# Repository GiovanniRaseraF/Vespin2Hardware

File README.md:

# Hardware
## Modulo LM2596S
### Autors
- Cristofoli Nicola : Schematics
- Rasera Giovanni : PCB layout

-

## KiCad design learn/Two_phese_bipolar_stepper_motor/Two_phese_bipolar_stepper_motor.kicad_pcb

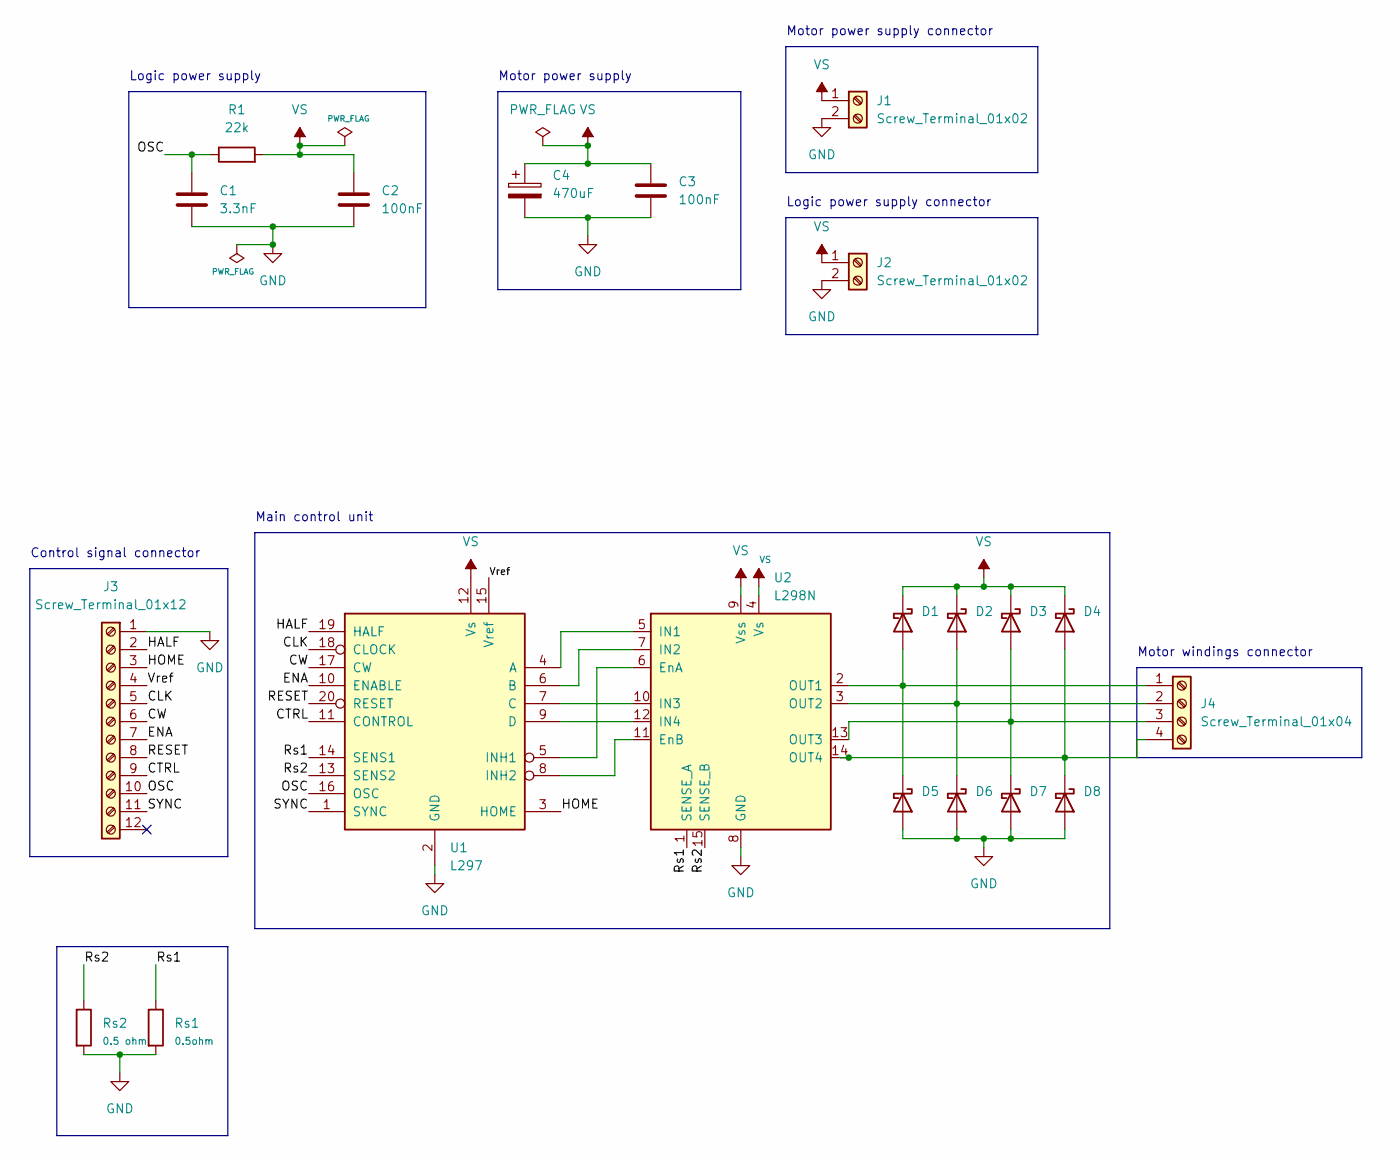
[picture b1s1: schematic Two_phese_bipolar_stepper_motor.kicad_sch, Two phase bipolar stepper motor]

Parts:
C1: 3.3nF; C_Rect_L10.0mm_W3.0mm_P7.50mm_FKS3_FKP3
C2, C3: 100nF; C_Rect_L7.5mm_W6.5mm_P5.00mm
C4: 470uF; CP_Radial_D13.0mm_P5.00mm
D1, D2, D3, D4, D5, D6, D7, D8: D_DO-27_P15.24mm_Horizontal
J1, J2: Screw_Terminal_01x02; TerminalBlock_Phoenix_MKDS-1,5-2-5.08_1x02_P5.08mm_Horizont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
J3: Screw_Terminal_01x12; TerminalBlock_Phoenix_MKDS-1,5-12_1x12_P5.00mm_Horizontal
J4: Screw_Terminal_01x04; TerminalBlock_Phoenix_MKDS-1,5-4_1x04_P5.00mm_Horizontal
R1: 22k; R_Axial_DIN0922_L20.0mm_D9.0mm_P25.40mm_Horizontal
Rs1: 0.5ohm; R_Axial_DIN0414_L11.9mm_D4.5mm_P15.24mm_Horizontal
Rs2: 0.5 ohm; R_Axial_DIN0414_L11.9mm_D4.5mm_P15.24mm_Horizontal
U1: L297; DIP-20_W7.62mm_LongPads
U2: L298N; TO-220-15_P2.54x2.54mm_StaggerOdd_Lead4.58mm_Vertical

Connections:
/CLK: J3.5, U1.18 (CLOCK)
/CTRL: J3.9, U1.11 (CONTROL)
/CW: J3.6, U1.17 (CW)
/ENA: J3.7, U1.10 (ENABLE)
/HALF: J3.2, U1.19 (HALF)
/HOME: J3.3, U1.3 (HOME)
/OSC: C1.1, J3.10, R1.1, U1.16 (OSC)
/RESET: J3.8, U1.20 (RESET)
/Rs1: Rs1.1, U1.14 (SENS1), U2.1 (SENSE_A)
/Rs2: Rs2.1, U1.13 (SENS2), U2.15 (SENSE_B)
/SYNC: J3.11, U1.1 (SYNC)
/Vref: J3.4, U1.15 (Vref)
GND: C1.2, C2.2, C3.2, C4.2, D5.2 (A), D6.2 (A), D7.2 (A), D8.2 (A), J1.2, J2.2, J3.1, Rs1.2, Rs2.2, U1.2 (GND), U2.8 (GND)
unnamed: D1.2 (A), D5.1 (K), J4.1, U2.2 (OUT1)
unnamed: D2.2 (A), D6.1 (K), J4.2, U2.3 (OUT2)
unnamed: D3.2 (A), D7.1 (K), J4.3, U2.13 (OUT3)
unnamed: D4.2 (A), D8.1 (K), J4.4, U2.14 (OUT4)
unnamed: U1.4 (A), U2.5 (IN1)
unnamed: U1.6 (B), U2.7 (IN2)
unnamed: U1.7 (C), U2.10 (IN3)
unnamed: U1.9 (D), U2.12 (IN4)
unnamed: U1.5 (INH1), U2.6 (EnA)
unnamed: U1.8 (INH2), U2.11 (EnB)
VS: C2.1, C3.1, C4.1, D1.1 (K), D2.1 (K), D3.1 (K), D4.1 (K), J1.1, J2.1, R1.2, U1.12 (Vs), U2.4 (Vs), U2.9 (Vss)

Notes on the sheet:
Logic power supply
Motor power supply connector
Main control unit
Motor power supply
Motor windings connector
Control signal connector
Logic power supply connector

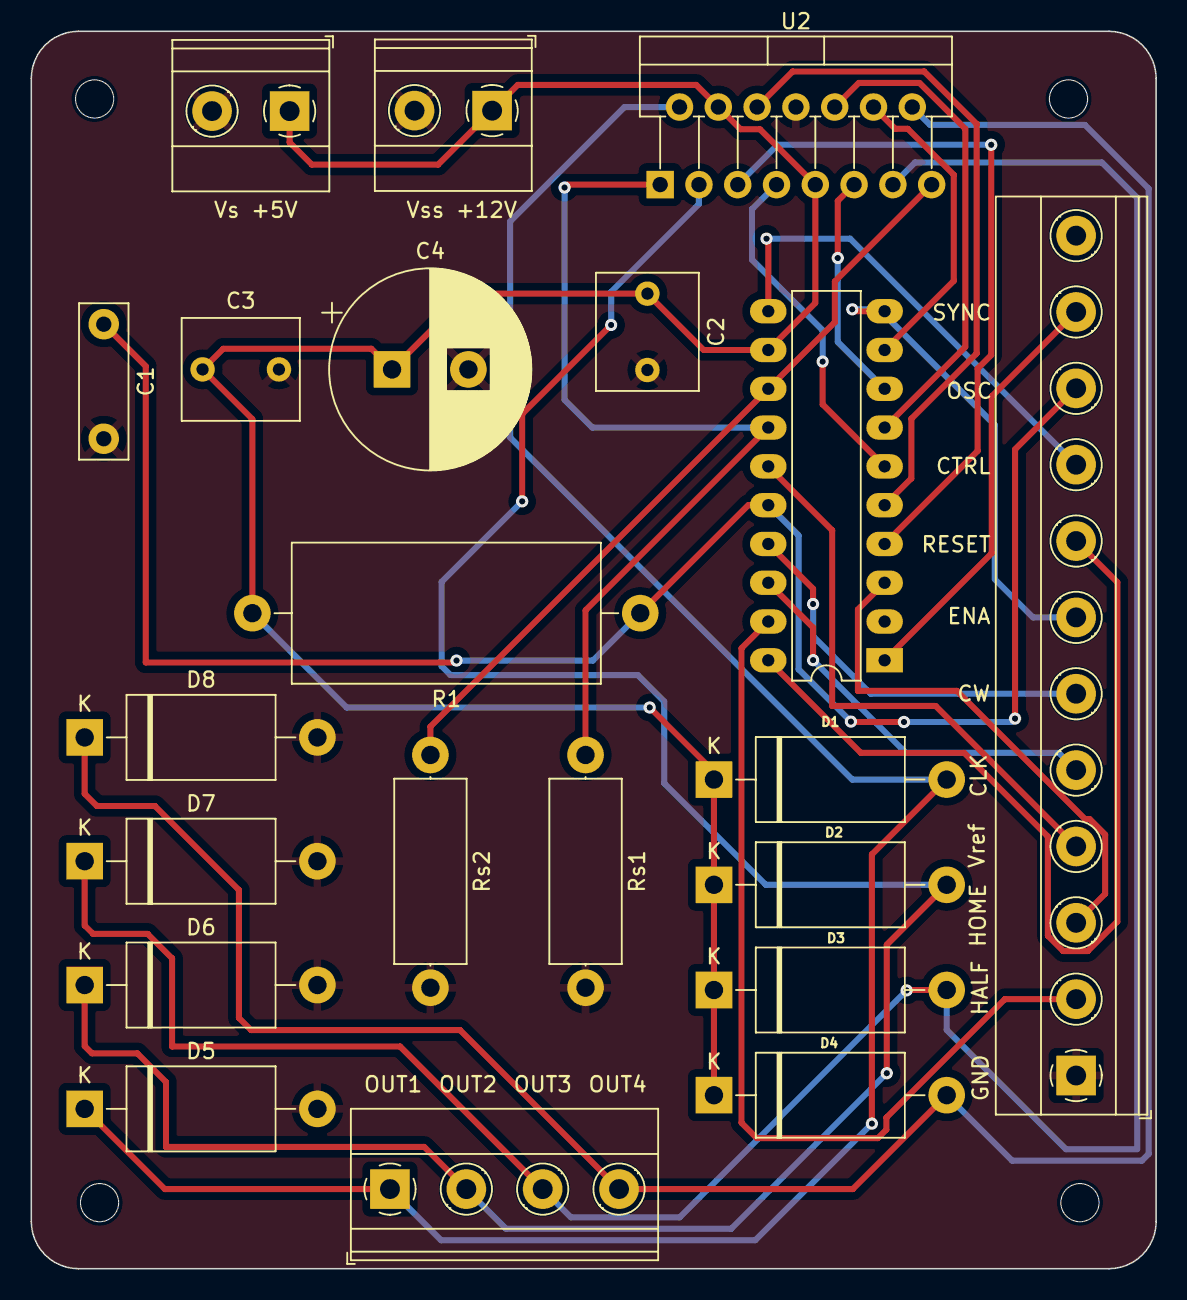
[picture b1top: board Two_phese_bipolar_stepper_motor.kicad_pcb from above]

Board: 2 copper layers, 73.7 x 81.0 mm, 21 parts (0 on the bottom side), 24 nets.

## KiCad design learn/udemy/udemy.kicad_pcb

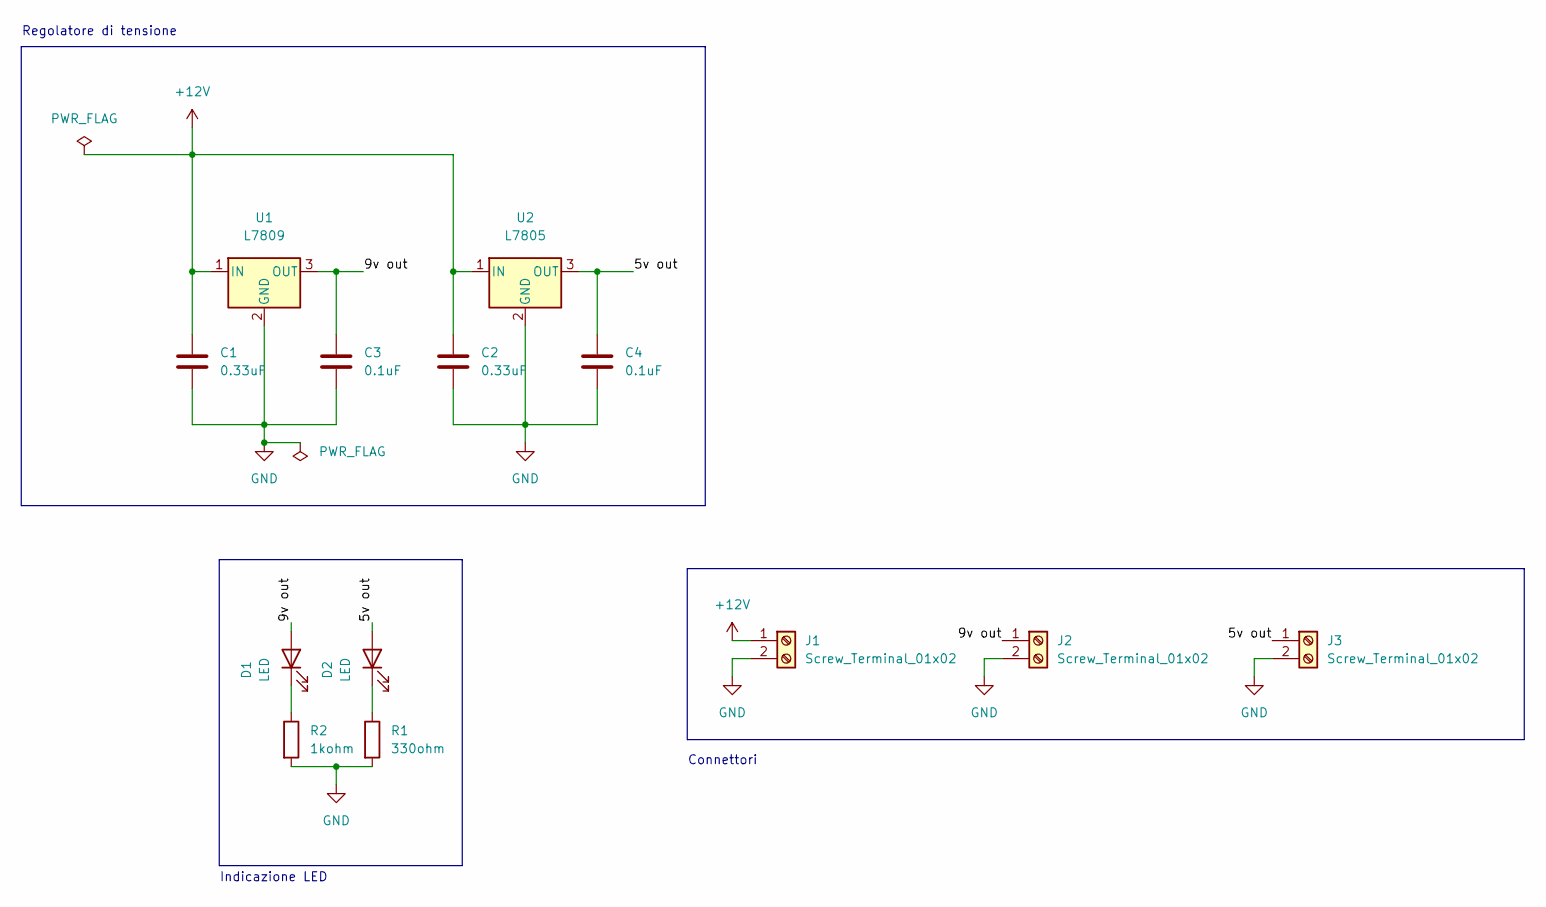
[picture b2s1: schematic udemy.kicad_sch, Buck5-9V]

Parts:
C1, C2: 0.33uF; C_Disc_D4.7mm_W2.5mm_P5.00mm
C3, C4: 0.1uF; C_Disc_D3.0mm_W2.0mm_P2.50mm
D1, D2: LED; LED_D4.0mm
J1, J2, J3: Screw_Terminal_01x02; TerminalBlock_Phoenix_MKDS-1,5-2-5.08_1x02_P5.08mm_Horizont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
R1: 330ohm; R_Axial_DIN0204_L3.6mm_D1.6mm_P5.08mm_Horizontal
R2: 1kohm; R_Axial_DIN0207_L6.3mm_D2.5mm_P7.62mm_Horizontal
U1: L7809; TO-220-3_Vertical
U2: L7805; TO-220-3_Vertical

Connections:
+12V: C1.1, C2.1, J1.1, U1.1 (IN), U2.1 (IN)
/5v out: C4.1, D2.2 (A), J3.1, U2.3 (OUT)
/9v out: C3.1, D1.2 (A), J2.1, U1.3 (OUT)
GND: C1.2, C2.2, C3.2, C4.2, J1.2, J2.2, J3.2, R1.2, R2.2, U1.2 (GND), U2.2 (GND)
unnamed: D1.1 (K), R2.1
unnamed: D2.1 (K), R1.1

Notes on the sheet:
Connettori
Indicazione LED
Regolatore di tensione

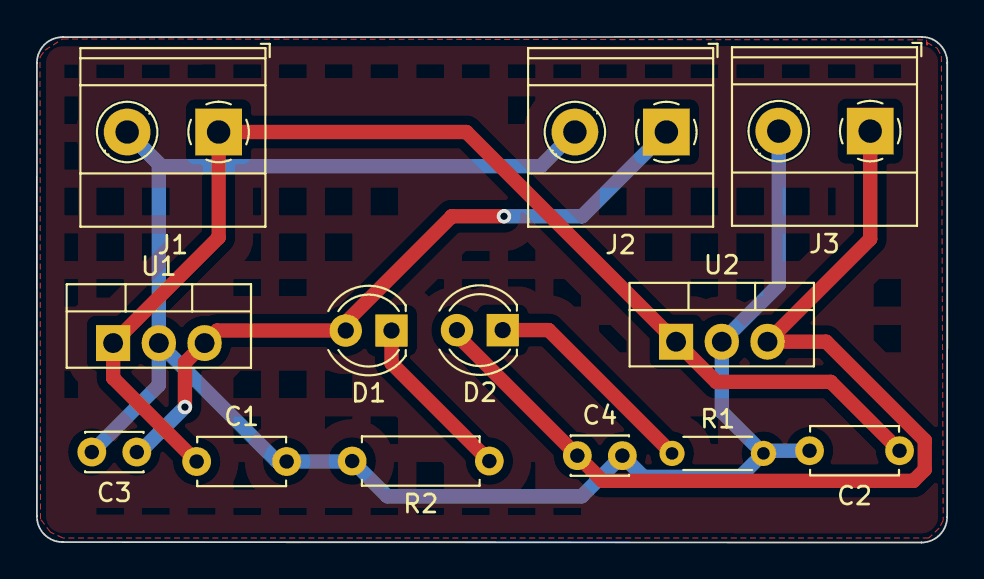
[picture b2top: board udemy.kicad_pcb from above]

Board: 2 copper layers, 50.6 x 28.1 mm, 13 parts (0 on the bottom side), 6 nets.

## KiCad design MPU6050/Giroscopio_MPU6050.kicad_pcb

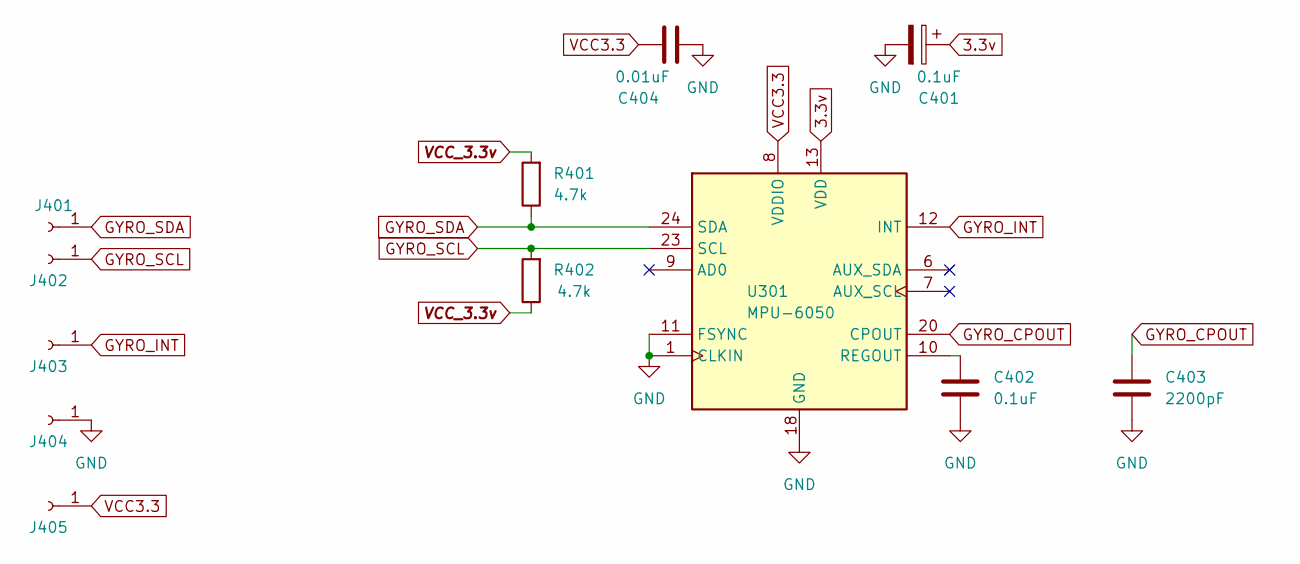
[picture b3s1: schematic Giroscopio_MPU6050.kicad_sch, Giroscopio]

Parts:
C401: 0.1uF; CP_EIA-1608-08_AVX-J
C402: 0.1uF; C_0805_2012Metric
C403: 2200pF; C_0805_2012Metric
C404: 0.01uF; C_0805_2012Metric
J401, J402, J403, J404, J405: Conn_01x01_Female; TestPoint_Pad_1.0x1.0mm
R401, R402: 4.7k; R_0805_2012Metric
U301: MPU-6050; InvenSense_QFN-24_4x4mm_P0.5mm

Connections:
3.3v: C401.1, U301.13 (VDD)
GND: C401.2, C402.2, C403.1, C404.1, J404.1, U301.1 (CLKIN), U301.11 (FSYNC), U301.18 (GND)
GYRO_CPOUT: C403.2, U301.20 (CPOUT)
GYRO_INT: J403.1, U301.12 (INT)
GYRO_SCL: J402.1, R402.2, U301.23 (SCL)
GYRO_SDA: J401.1, R401.1, U301.24 (SDA)
unnamed: C402.1, U301.10 (REGOUT)
VCC3.3: C404.2, J405.1, U301.8 (VDDIO)
VCC_3.3v: R401.2, R402.1

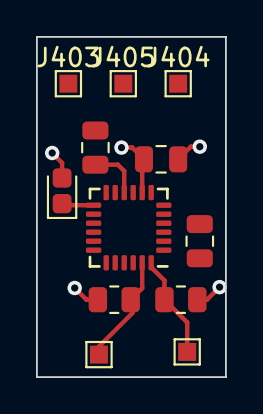
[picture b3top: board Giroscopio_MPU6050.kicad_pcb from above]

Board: 2 copper layers, 10.5 x 18.9 mm, 12 parts (0 on the bottom side), 9 nets.

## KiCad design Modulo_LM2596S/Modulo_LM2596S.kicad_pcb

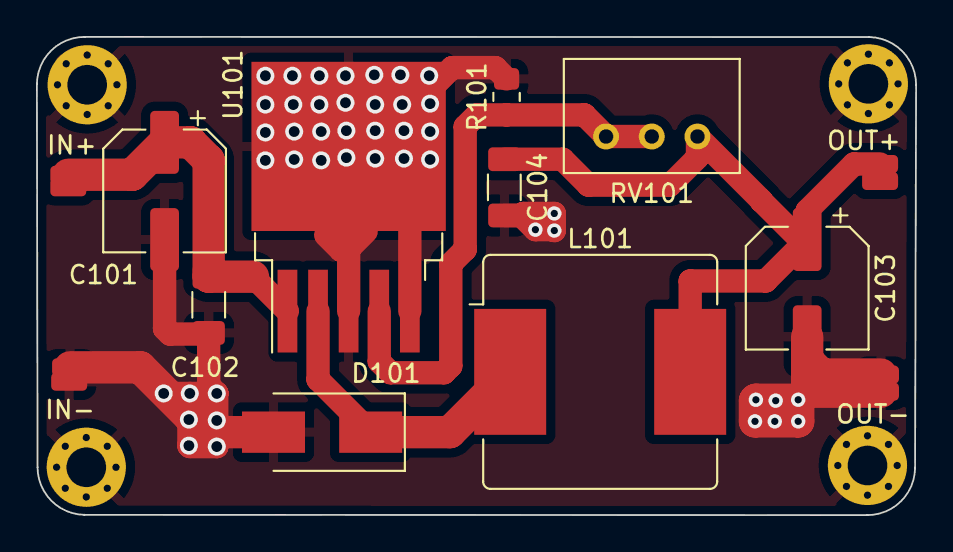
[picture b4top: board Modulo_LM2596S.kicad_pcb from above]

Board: 2 copper layers, 48.8 x 26.6 mm, 21 parts (0 on the bottom side), 5 nets.

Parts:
C101: 100uF; CP_Elec_6.3x3.9
C102, C104: 1uF; C_1206_3216Metric_Pad1.33x1.80mm_HandSolder
C103: 220uF; CP_Elec_6.3x3.9
D101: SS34; D_SMB_Handsoldering
H101, H102, H103, H104: MountingHole_Pad; MountingHole_2.2mm_M2_Pad_Via
J101, J102, J103, J104, J105, J106, J107, J108: Conn_01x01_Female; SolderWirePad_1x01_SMD_1x2mm
L101: 47uH; L_Bourns_SRR1208_12.7x12.7mm
R101: 330; R_0805_2012Metric_Pad1.20x1.40mm_HandSolder
RV101: 10k; Potentiometer_Bourns_3299W_Vertical
U101: LM2596S-ADJ; TO-263-5_TabPin3

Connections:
unnamed: D101.1 (K), L101.1, U101.2 (OUT)
unnamed: R101.1, RV101.1, RV101.2, U101.4 (FB)
OUT+: C103.1, C104.1, J103.1, J107.1, L101.2, RV101.3
OUT-: C101.2, C102.2, C103.2, C104.2, D101.2 (A), H101.1, H102.1, H103.1, H104.1, J102.1, J104.1, J106.1, J108.1, R101.2, U101.3 (GND), U101.5 (~ON/OFF)
Vin+: C101.1, C102.1, J101.1, J105.1, U101.1 (VIN)

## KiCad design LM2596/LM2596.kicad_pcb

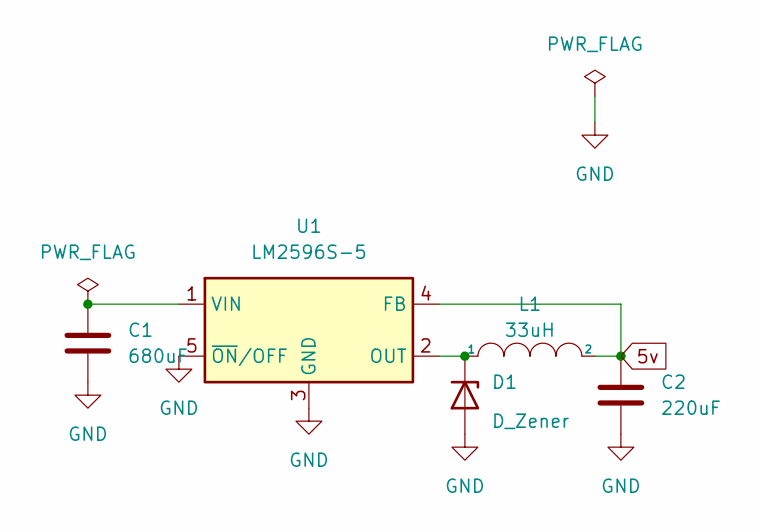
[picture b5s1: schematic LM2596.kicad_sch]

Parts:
C1: 680uF; CP_Elec_3x5.3
C2: 220uF; CP_Elec_3x5.3
D1: D_Zener; D_0201_0603Metric
L1: 33uH; L_6.3x6.3_H3
U1: LM2596S-5; TO-263-5_TabPin3

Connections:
5v: C2.1, L1.2, U1.4 (FB)
GND: C1.1, C2.2, D1.2 (A), U1.3 (GND), U1.5 (~ON/OFF)
unnamed: C1.2, U1.1 (VIN)
unnamed: D1.1 (K), L1.1, U1.2 (OUT)

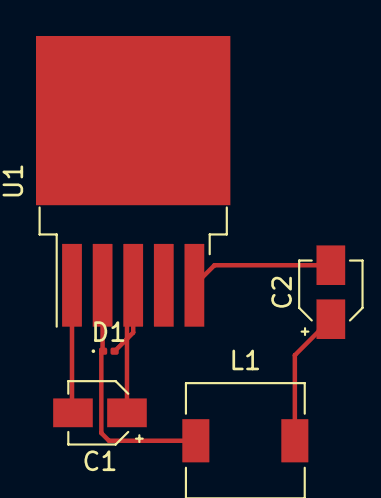
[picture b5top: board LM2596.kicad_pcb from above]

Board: 2 copper layers, 5 parts (0 on the bottom side), 4 nets.

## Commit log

2022-10-06 06/10/2022 aggiunto gnd
2022-10-09 09/10/2022
    prima volta
2022-10-09 LM3940
    Creata nuova cartella per LM3940
    Creato lo schema elettrico
2022-10-09 Aggiunto R
2022-10-09 Cancellato le resistenze
2022-10-09 La diagnostica mi da errore all'ingresso 3 del transistor, non trovo la soluzione
2022-10-09 Errore nel pin 3 del transistor
    Tutti gli errori sono stati eliminati, resta solo uno, quello nel pin 3 (Vin) del transistor.
    Non trovo una soluzione
2022-10-11 11/10/2022
    Circuito elettrico dell'LM2596
2022-10-11 Footprint e PCB
    Assegnazione delle footprint a tutti i componenti e collocato il tutto nel file PCB
2022-10-12 Git Ignore
2022-10-13 13/10/2022
    Sistemato lo schema elettrico.
    Creato le tracce nel file PCB.
2022-10-15 15/10/2022
    Ridisegnato il circuito PCB
2022-10-16 16/10/22
    Nessuna modifica
2022-10-17 Immagine di LM2596s
2022-10-17 Modulo LM2596S
    Schematica del modulo e annotazione da 100
2022-10-20 Footprint potenziometro (20/10/2022)
    Ho assegnato la footprint al potenziometro, controllare se è corretto.
    Il resto del circuito non è stato controllato
2022-10-21 Aggiunta di commento su potenziometro
2022-10-21 gitignore
2022-10-22 Test delle metriche (22/10/2022)
    Solo un test, non è finale o completo.
2022-10-23 Footprint (tentativo fallito)
    23/10/2022 tentato di assegnare le footprint a tutti i componenti dello schema logico, ma senza successo
2022-10-24 LM2596S: creazione della scheda fisica
    Selezione dei componenti e creazione del PCB.
    TODO: Da mettere a posto le tracce @GiovanniRaseraF
2022-10-24 Aggiornamento da Nicola
2022-10-24 Aggiornamento da Giovanni
2022-10-24 Risolto il merge di nicola
2022-10-25 LM2596: Finito di tirare le tracce
    Tirato le tracce e il piano di GND
    Inserito io MountPad ed i punti di solder dei cavi di input e output
2022-10-25 25/10/2022 MPU6050
    Immagine del modulo MPU6050
2022-10-25 Creata nuova cartella MPU6050
    Creata la nuova cartella MPU6050 e al suo interno sono stati aggiunti i file sch e pcb del giroscopio.
2022-10-25 LM2596S: Creazione del layout e inserimento dei solderpoints
2022-10-25 Images: Aggiunta della foto del PCB
2022-10-25 README: Correzione di ortografia
2022-10-26 MPU6050: Anotazione da 400
2022-10-26 MPU6050: Ci sono degli errori di collegamento su sda e scl
2022-10-26 LM2596S: Ordine della scheda da JLCPCB
2022-10-27 Images: Foto di LM2596S cambiata
2022-10-28 LM2596S: Test di fillzone
2022-10-28 MAIN: Pulizia delle cartelle e dei nomi delle sezioni
    Aggiunta della sezione old, dove stanno tutte le cartelle di test e cose vecchie
2022-10-31 main: pulizia
2022-11-05 MPU6050: controllo delle tracce
2022-11-07 MPU6050: controllo delle tracce e riorganizzazione
2022-11-09 MPU6050: creazione PBC
    Selezionato il footprint, tirato le tracce con EdgeCuts.
2022-11-10 MPU6050: modificato il leggermente il disegno
2022-11-11 main: fix typo
2022-11-15 MPU6050: aggiornamento della schematica
2022-11-16 MPU6050: creazione del PCB e layout NON completo
2022-11-16 mpu6050: aggiunta label e testpoint
2022-11-17 mpu6050: aggiunta testpad
2022-12-23 23/12/22 progetto del corso
    Creazione nuova cartella con relativi file.
2022-12-26 26/12/22 inizio collegamento
    Stesura dei primi fili.
    (Attenzione, schema non ancora completato)
2022-12-27 27/12/22 continuazione circuito elettrico
    Aggiunto delle nuove componenti e risolto bug.
2023-01-02 02/01/23 Utilizzo delle lable
2023-01-03 03/01/23 tutorial comandi menù
2023-01-05 05/01/23 modifiche al circuito elettrico
2023-01-06 06/01/23 assegnazione footprint
2023-01-07 07/01/23 inizio PCB
2023-01-08 08/01/23 sistemato i componenti nella pcb
2023-01-09 09/01/23 angoli smussati
2023-01-12 12/01/23 incisione vie
    Settaggio dei parametri per tracciare le vie di collegamento.
    Utilizzo dello strumento: calcolatrice.
    Inizio tracciatura vie (blu, quindi del retro del PCB)
2023-01-13 13/01/2023 continuazione col collegamento del e PCB
2023-01-15 15/01/23 correzione pcb tracce
    Bisogna aumentare la portata delle tracce
2023-01-18 18/01/23 correzione PCB
2023-01-22 22/01/23 aggiunto testo nel retro del PCB
2023-01-23 23/01/23 aggiunte quote del pcb
2023-01-29 29/01/23 aggiunti file mappa
2023-02-08 08/02/23 creato cartella "drill file"
2023-02-21 21/02/23 creazione nuovo file
2023-02-21 21/02/23 inserito tutti i componenti necessari per il nuovo progetto.
2023-02-22 22/02/23 L298N
    Ora sono presenti tutti i componenti per creare il progetto.
2023-02-25 25/02/23 Inizio collegamento (shc)
2023-03-01 01/03/23 aggiunto PWR_FLAG
2023-03-02 02/03/23 aggiunti diodi Zener
    Inizio collegamento del L298N
2023-03-06 06/03/23 avanzamento corso...
2023-03-08 Inizio collegamento L297 con L298N
2023-03-13 Avanzamento corso....
2023-03-14 Modifiche disegno. (nessun avanzamento)
2023-03-15 Avanzamento corso
2023-05-25 hw: copy and past
2023-06-04 04/06/2023 etichettature
2023-06-04 04/06/2023 inizio assegnazione impronte
2023-06-10 10/06/2023 write the footprint
2023-06-11 11/06/2023 start with pcb
2023-06-12 12/06/2023 make a pcb
2023-06-14 two_phese: made PCB
2023-06-15 two_phase_motor: made pcb
2023-06-15 Two_phase: print the wire
2023-06-15 images
2023-06-16 nothing
2023-06-19 two_phase: made pcb
2023-06-19 two_phase: made a pcb
2023-06-20 txo_phase: made pcb
2023-06-21 two_phase: clean the wrong wire and to do the new wire. Now the pcb is finisc
2023-06-22 two_phase: labeling the connectors
2023-06-26 two_phase: new lablel out 1 out2 out3 out4
2023-06-26 two_phase: new lablel
2023-06-26 two_phase: create fil gerber, bom, and drill
    the pcb rev1 is finished. the the connections haven't error
2023-06-27 project_3: start
    In this file, there are all photo of the project 3.
2023-06-27 certificato_di_completamento_del_corso
2023-06-28 udemy_kicad
2023-07-14 learn: create a new file: inventor
